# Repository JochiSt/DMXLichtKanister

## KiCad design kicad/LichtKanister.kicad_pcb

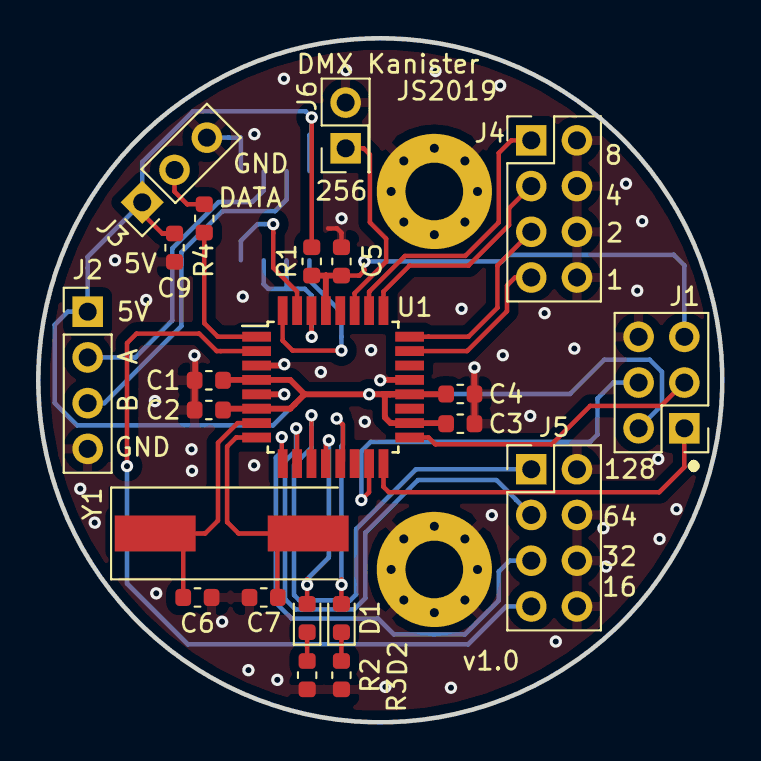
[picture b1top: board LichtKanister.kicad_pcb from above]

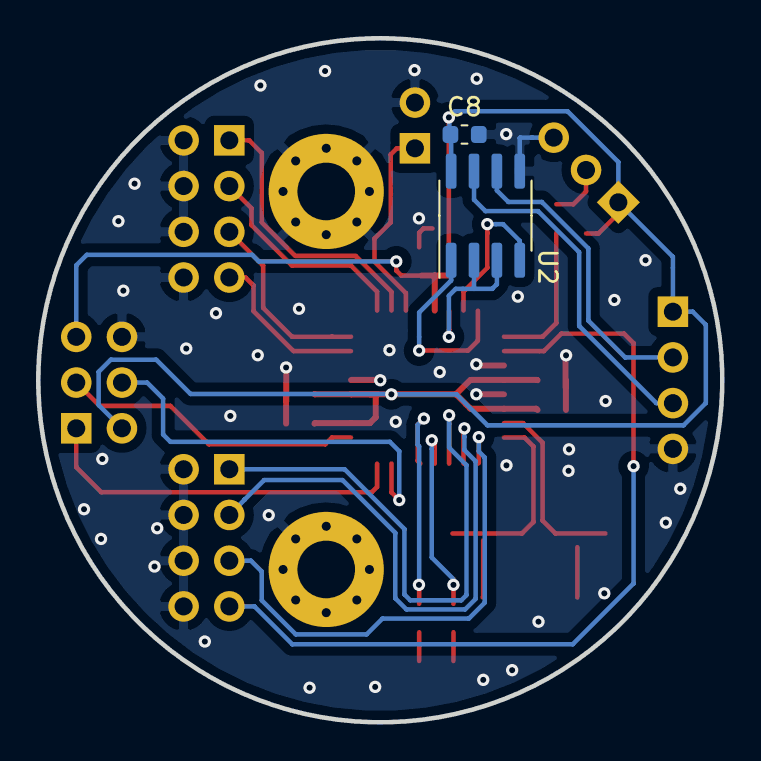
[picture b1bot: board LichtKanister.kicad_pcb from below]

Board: 2 copper layers, 38.0 x 38.0 mm, 26 parts (2 on the bottom side), 28 nets.

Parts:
C1, C2, C3, C4, C5, C8, C9: 100n; C_0603_1608Metric
C6, C7: 22p; C_0603_1608Metric
D1, D2: LED; LED_0603_1608Metric
H1, H2: MountingHole_Pad; MountingHole_3.2mm_M3_Pad_Via
J1: AVR-ISP-6; PinHeader_2x03_P2.54mm_Vertical
J2: Conn_01x04; PinHeader_1x04_P2.54mm_Vertical
J3: Conn_01x03; PinHeader_1x03_P2.54mm_Vertical
J4, J5: Conn_02x04_Odd_Even; PinHeader_2x04_P2.54mm_Vertical
J6: Conn_02x01; PinHeader_2x01_P2.54mm_Vertical
R1: 10k; R_0603_1608Metric
R2, R3, R4: R; R_0603_1608Metric
U1: ATmega48-20AU; TQFP-32_7x7mm_P0.8mm
U2: MAX485E; SOIC-8_3.9x4.9mm_P1.27mm
Y1: Crystal; Crystal_SMD_HC49-SD

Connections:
+5V: C1.1, C2.1, C3.1, C4.1, C8.1, C9.1, J1.2, J2.1, J3.1, R1.1, U1.4, U1.6, U1.18, U1.20, U2.8
/A: J2.2, U2.6
/ADDR1: J4.7, U1.23
/ADDR2: J4.5, U1.24
/ADDR4: J4.3, U1.25
/ADDR8: J4.1, U1.26
/ADDR16: J5.7, U1.2
/ADDR32: J5.5, U1.9
/ADDR64: J5.3, U1.10
/ADDR128: J5.1, U1.11
/ADDR256: J6.1, U1.27
/B: J2.3, U2.7
/DR: U1.30, U2.2, U2.3
/MISO: J1.1, U1.16
/MOSI: J1.4, U1.15
/RESET: C5.1, J1.5, R1.2, U1.29
/RXD: U1.32, U2.1
/SCK: J1.3, U1.17
/TXD: U1.31, U2.4
/WS2812_DATA: R4.1, U1.1
GND: C1.2, C2.2, C3.2, C4.2, C5.2, C6.1, C7.1, C8.2, C9.2, H1.1, H2.1, J1.6, J2.4, J3.3, J4.2, J4.4, J4.6, J4.8, J5.2, J5.4, J5.6, J5.8, J6.2, R2.1, R3.1, U1.3, U1.5, U1.21, U2.5
unnamed: C6.2, U1.7, Y1.1
unnamed: C7.2, U1.8, Y1.2
unnamed: D1.1, R2.2
unnamed: D1.2, U1.12
unnamed: D2.1, R3.2
unnamed: D2.2, U1.13
unnamed: J3.2, R4.2

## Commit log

2019-10-08 added first version of firmware (first try of implementation)
2019-10-08 added layout of first version of PCB
2019-10-08 very small change, just enabled all layers
2019-10-08 moved layout to correct folder
2019-10-20 added Mounting Holes, PinHeader for addressing first iteration of routing done
2019-10-20 fixed DRC violations
